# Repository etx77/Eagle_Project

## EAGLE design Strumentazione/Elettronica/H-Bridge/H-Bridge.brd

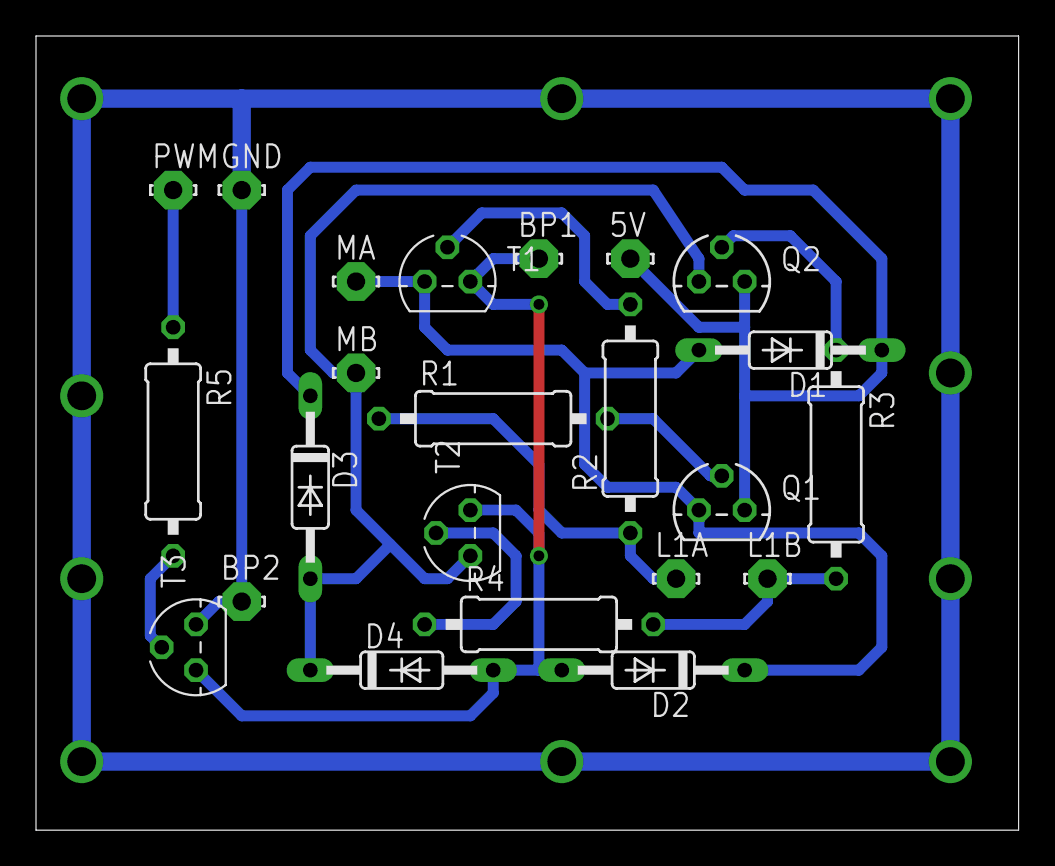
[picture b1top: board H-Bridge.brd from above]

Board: 2 copper layers, 54.6 x 44.1 mm, 23 parts (0 on the bottom side), 13 nets.

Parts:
5V: LSP10
BP1, BP2: LSP10
D1, D2, D3, D4: 1N4148DO35-10; DO35-10
GND: LSP10
L1A, L1B: LSP10
MA: LSP10
MB: LSP10
PWM: LSP10
Q1, Q2: BC557; TO92
R1, R2, R3, R4: 10k; 0309/12
R5: 1k2; 0309/12
T1, T2, T3: BC547; TO92

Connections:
unnamed: L1A.MP, R1.1, R2.1
unnamed: Q1.2, R1.2
unnamed: R2.2, T1.2
unnamed: D1.A, D2.C, MA.MP, Q1.3, T1.3
unnamed: D3.A, D4.C, MB.MP, Q2.3, T2.3
unnamed: Q2.2, R3.1
unnamed: R4.1, T2.2
unnamed: L1B.MP, R3.2, R4.2
unnamed: BP1.MP, D2.A, D4.A, T1.1, T2.1, T3.3
unnamed: 5V.MP, D1.C, D3.C, Q1.1, Q2.1
unnamed: R5.2, T3.2
unnamed: PWM.MP, R5.1
unnamed: BP2.MP, GND.MP, T3.1

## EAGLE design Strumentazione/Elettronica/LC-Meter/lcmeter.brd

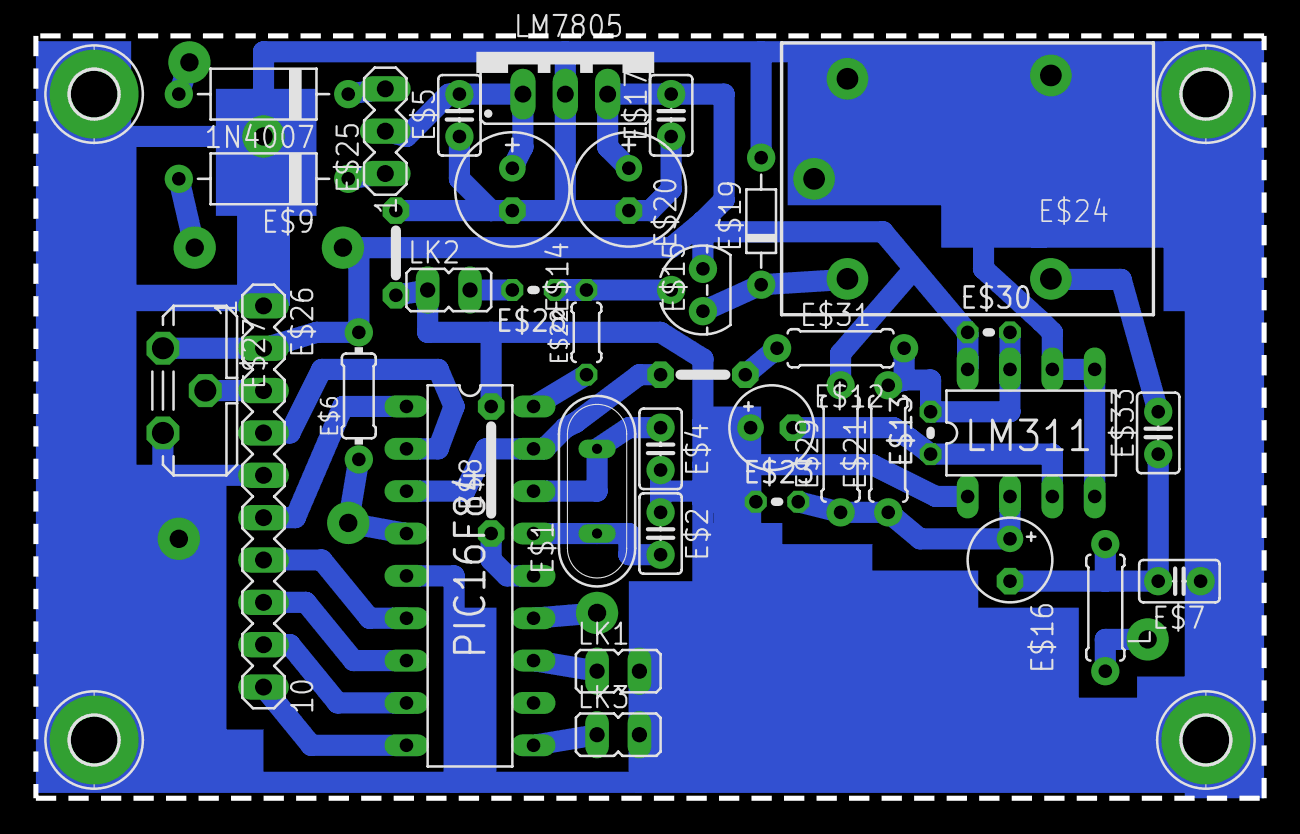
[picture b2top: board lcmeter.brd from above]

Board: 2 copper layers, 73.7 x 45.7 mm, 42 parts (0 on the bottom side), 29 nets.

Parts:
1N4007: 1N4007; D-10
E$1: 4MHz; QS
E$2, E$4: 33pF; C2.5-2
E$3: Vcc; 05
E$5, E$17: 0.1; C2.5-2
E$6: 6.8K; 0204/7
E$7, E$33: 1nF; C2.5-2
E$8: 07
E$9: 1N4007; D-10
E$12, E$16: 10uF; E2,5-5
E$13: 47K; 0204V
E$14, E$15: 22uF; E2,5-7
E$19: 1N914; D-7.5
E$20: PNP; TO92
E$21, E$29: 100K; 0207/7
E$22: 6.8K; 0204/5
E$23: 100K; 0204V
E$24: Rele; ZN5
E$25: MA03-1
E$26: MA10-1
E$27: 10K; ST10
E$28: 6.8K; 0204V
E$30: 1K; 0204V
E$31: 6.8K; 0207/7
E$32: 05
E$34, E$35, E$36, E$37: 2,8-PAD
L: 82uH; 0207/7
LK1, LK2, LK3: JP1
LM311: LM311; DIL8
LM7805: LM7805; 78XXS
PIC16F84: PIC16F84; DIL18

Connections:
GND: E$2.1, E$3.1, E$3.2, E$4.2, E$5.1, E$8.2, E$14.-, E$15.-, E$17.1, E$19.A, E$23.1, E$24.11, E$26.1, E$26.5, LK1.2, LK2.1, LK3.2, LM311.1, LM7805.GND, PIC16F84.5
S$2: E$1.1, E$2.2, PIC16F84.15
S$3: E$9.C, E$25.1
S$4: E$1.2, E$4.1, PIC16F84.16
S$5: E$30.1, LM311.8
S$6: 1N4007.C, E$25.3
S$7: E$26.6, PIC16F84.1
S$8: E$26.3, E$27.S
S$9: E$5.2, E$14.+, E$25.2, LM7805.IN
S$10: E$26.4, PIC16F84.2
S$11: E$13.1, LM311.3
S$13: LK3.1, PIC16F84.10
S$14: E$28.2, LK2.2
S$15: E$20.2, E$28.1
S$17: E$19.C, E$20.1
S$19: E$6.1, PIC16F84.4
S$22: E$30.2, LM311.7
S$23: E$21.1, E$23.2
S$24: E$21.2, E$31.2
S$27: E$32.1, PIC16F84.3, PIC16F84.17
S$28: E$31.1, E$32.2
S$29: E$16.-, E$33.1, L.1
S$30: E$26.10, PIC16F84.9
S$32: E$26.8, PIC16F84.7
S$33: E$26.7, PIC16F84.6
S$34: LK1.1, PIC16F84.12
S$36: LM311.5, LM311.6
S$37: E$8.1, PIC16F84.14
VCC: E$9.A, E$15.+, E$17.2, E$20.3, E$26.2, E$27.A, L.2, LM7805.OUT, PIC16F84.13

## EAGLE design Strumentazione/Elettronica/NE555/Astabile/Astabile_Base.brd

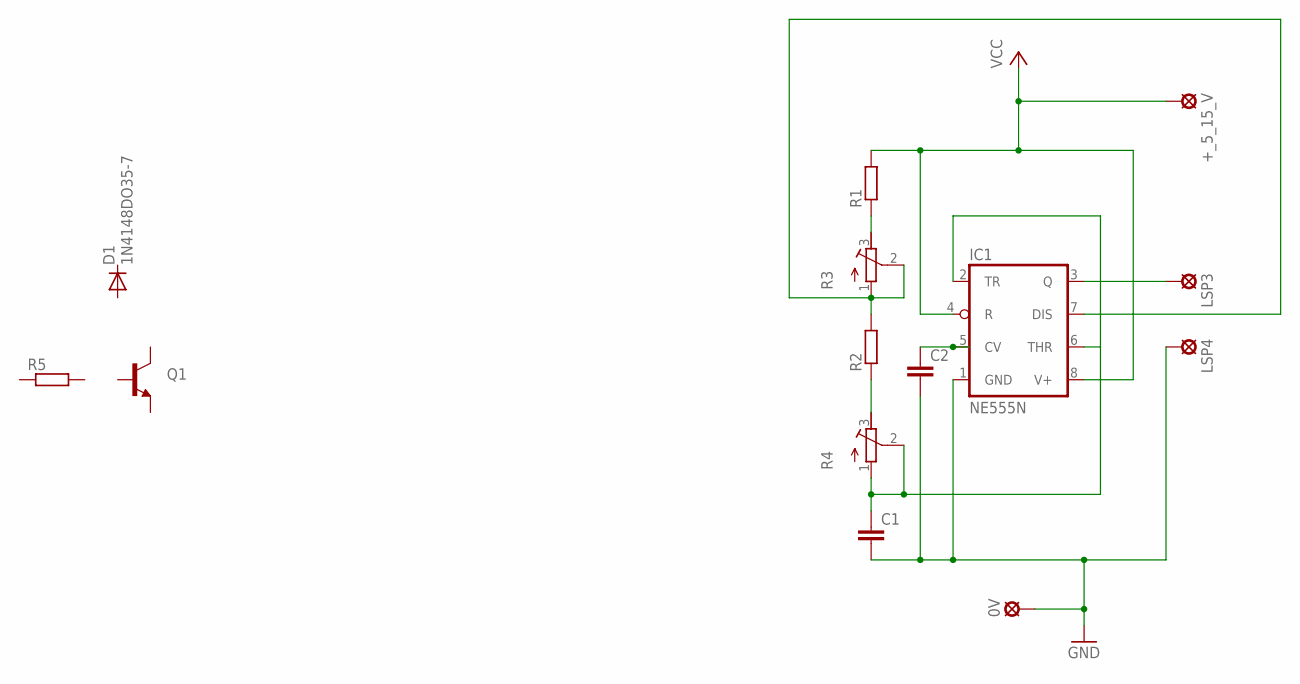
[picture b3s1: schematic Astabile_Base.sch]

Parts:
0V: LSP10
+_5_15_V: LSP10
C1, C2: C-EU050-024X044; C050-024X044
D1: 1N4148DO35-7; DO35-7
IC1: NE555N; DIL08
LSP3, LSP4: LSP10
Q1: TRANSISTOR_NPNBC547; TO-92-AMMO
R1, R2: R-EU_0204/7; 0204/7
R3, R4: R-TRIMM3339P; RTRIM3339P
R5: R-EU_0207/2V; 0207/2V

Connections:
GND: 0V.MP, C1.2, C2.2, IC1.1 (GND), LSP4.MP
unnamed: IC1.3 (Q), LSP3.MP
unnamed: R1.1, R3.3 (E)
unnamed: IC1.7 (DIS), R2.2, R3.1 (A), R3.2 (S)
unnamed: R2.1, R4.3 (E)
unnamed: C1.1, IC1.2 (TR), IC1.6 (THR), R4.1 (A), R4.2 (S)
unnamed: C2.1, IC1.5 (CV)
VCC: +_5_15_V.MP, IC1.4 (R), IC1.8 (V+), R1.2

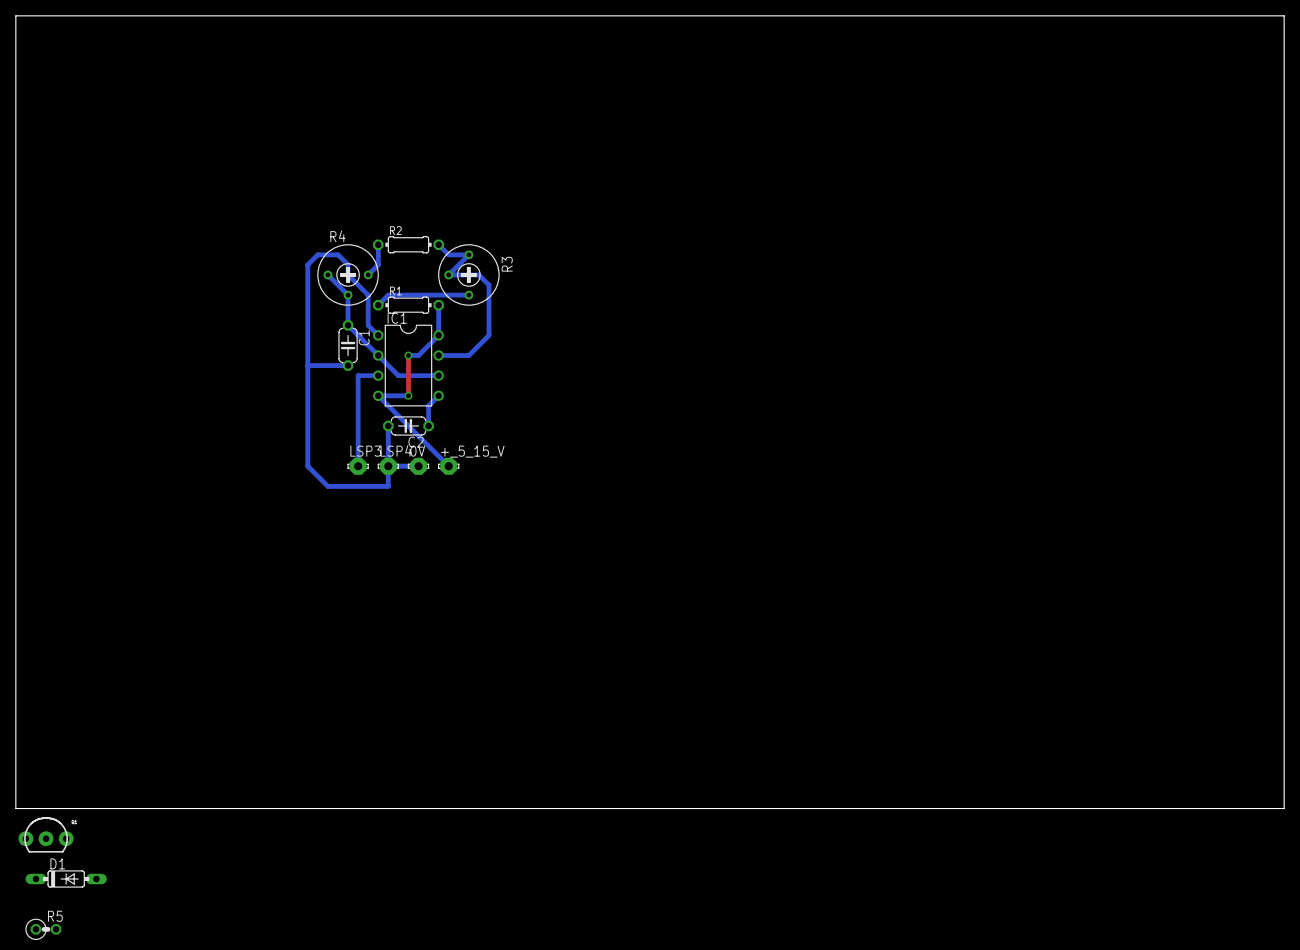
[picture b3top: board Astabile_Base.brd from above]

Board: 2 copper layers, 160.0 x 100.0 mm, 14 parts (0 on the bottom side), 8 nets.

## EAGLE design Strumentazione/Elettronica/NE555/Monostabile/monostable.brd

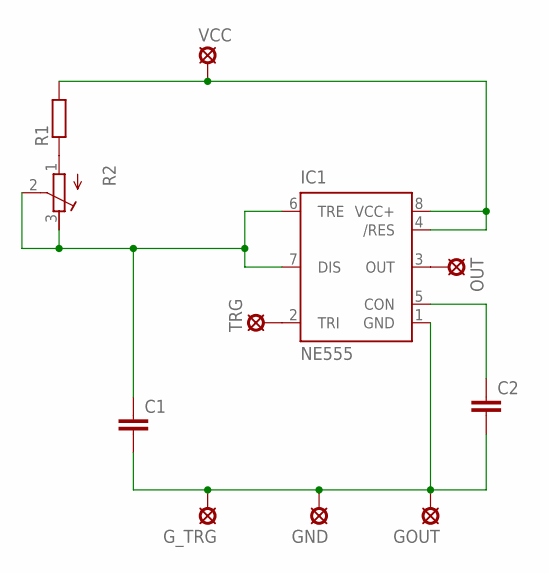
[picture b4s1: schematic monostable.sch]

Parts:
C1, C2: C-EU050-024X044; C050-024X044
GND: LSP10
GOUT: LSP10
G_TRG: LSP10
IC1: NE555; DIL-08
OUT: LSP10
R1: R-EU_0207/10; 0207/10
R2: R-TRIMM3339P; RTRIM3339P
TRG: LSP10
VCC: LSP10

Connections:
unnamed: C1.2, C2.2, GND.MP, GOUT.MP, G_TRG.MP, IC1.1 (GND)
unnamed: C1.1, IC1.6 (TRE), IC1.7 (DIS), R2.2 (S), R2.3 (E)
unnamed: C2.1, IC1.5 (CON)
unnamed: IC1.4 (/RES), IC1.8 (VCC+), R1.2, VCC.MP
unnamed: IC1.2 (TRI), TRG.MP
unnamed: IC1.3 (OUT), OUT.MP
unnamed: R1.1, R2.1 (A)

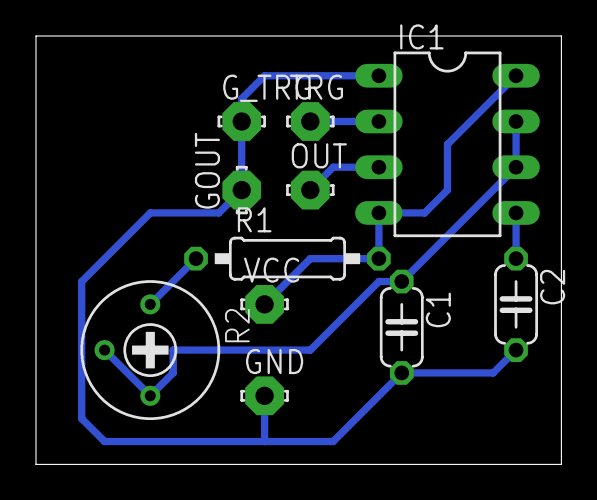
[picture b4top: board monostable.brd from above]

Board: 2 copper layers, 29.2 x 23.8 mm, 11 parts (0 on the bottom side), 7 nets.

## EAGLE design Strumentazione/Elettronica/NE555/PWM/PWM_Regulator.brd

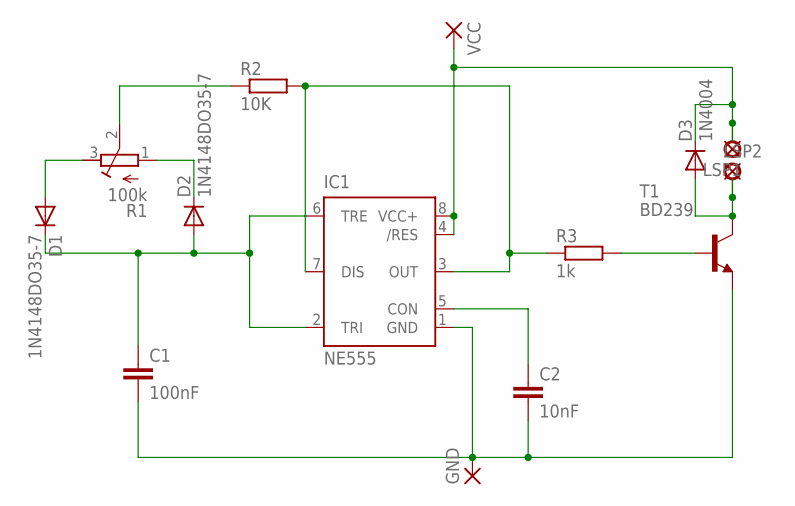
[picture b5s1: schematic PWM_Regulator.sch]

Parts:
C1: 100nF; C050-024X044
C2: 10nF; C050-024X044
D1, D2: 1N4148DO35-7; DO35-7
D3: 1N4004; DO41-10
GND: 2,54/0,8
IC1: NE555; DIL-08
LSP1, LSP2: LSP10
R1: 100k; RTRIM3339P
R2: 10K; 0204/7
R3: 1k; 0207/10
T1: BD239; TO220
VCC: 2,54/0,8

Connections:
unnamed: D1.A, R1.3 (E)
unnamed: D2.C, R1.1 (A)
unnamed: C1.1, D1.C, D2.A, IC1.2 (TRI), IC1.6 (TRE)
unnamed: R3.2, T1.1 (B)
unnamed: C2.1, IC1.5 (CON)
unnamed: D3.C, IC1.4 (/RES), IC1.8 (VCC+), LSP1.MP, VCC.1
unnamed: IC1.3 (OUT), IC1.7 (DIS), R2.2, R3.1
unnamed: R1.2 (S), R2.1
unnamed: C1.2, C2.2, GND.1, IC1.1 (GND), T1.3 (E)
unnamed: D3.A, LSP2.MP, T1.2 (C)

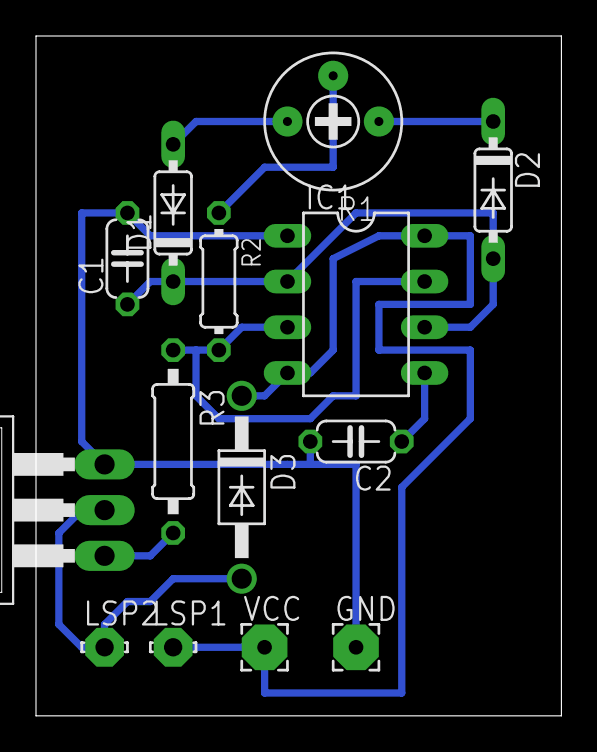
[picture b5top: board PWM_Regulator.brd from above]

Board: 2 copper layers, 29.2 x 37.8 mm, 14 parts (0 on the bottom side), 10 nets.

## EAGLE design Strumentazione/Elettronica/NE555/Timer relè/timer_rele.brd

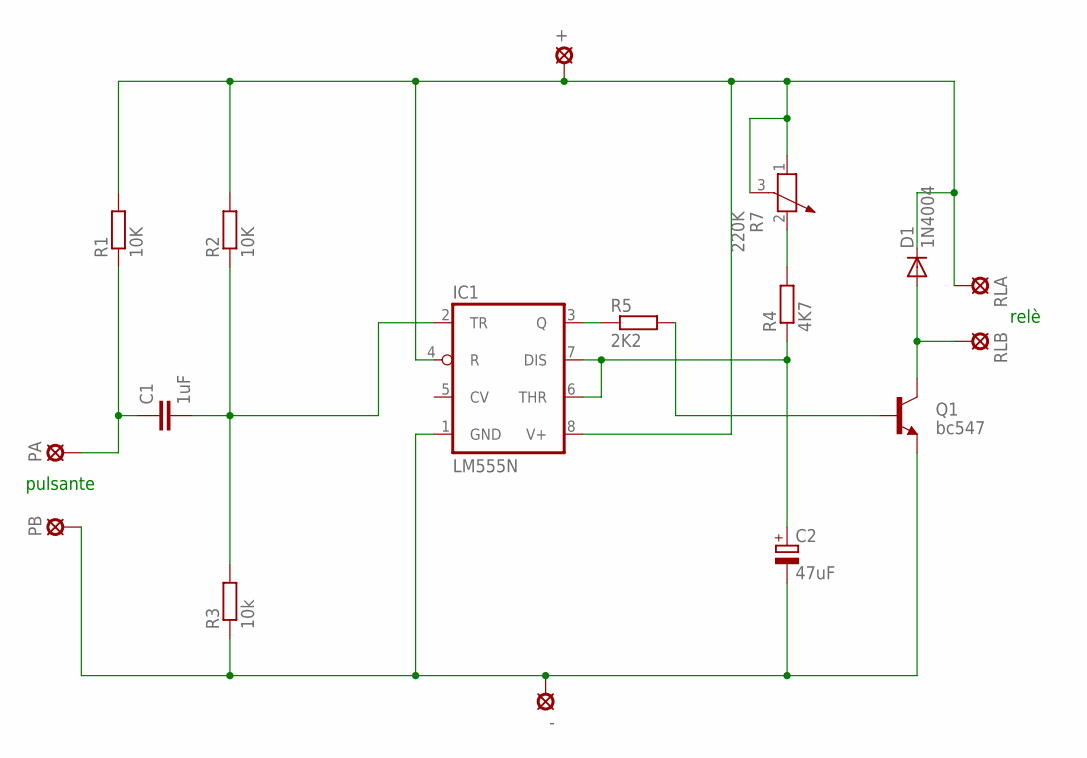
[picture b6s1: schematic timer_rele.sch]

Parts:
+: LSP10
-: LSP10
C1: 1uF; C050-030X075
C2: 47uF; E2-5
D1: 1N4004; DO41-10
IC1: LM555N; DIL08
PA: LSP10
PB: LSP10
Q1: bc547; TO-92-AMMO
R1, R2: 10K; 0207/10
R3: 10k; 0207/10
R4: 4K7; 0207/10
R5: 2K2; 0207/10
R7: 220K; PT-10
RLA: LSP10
RLB: LSP10

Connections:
unnamed: +.MP, D1.C, IC1.4 (R), IC1.8 (V+), R1.2, R2.2, R7.1, R7.3, RLA.MP
unnamed: D1.A, Q1.1 (C), RLB.MP
unnamed: -.MP, C2.-, IC1.1 (GND), PB.MP, Q1.3 (E), R3.1
unnamed: C1.1, PA.MP, R1.1
unnamed: C1.2, IC1.2 (TR), R2.1, R3.2
unnamed: IC1.3 (Q), R5.1
unnamed: Q1.2 (B), R5.2
unnamed: R4.2, R7.2
unnamed: C2.+, IC1.6 (THR), IC1.7 (DIS), R4.1

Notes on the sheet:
pulsante
relè

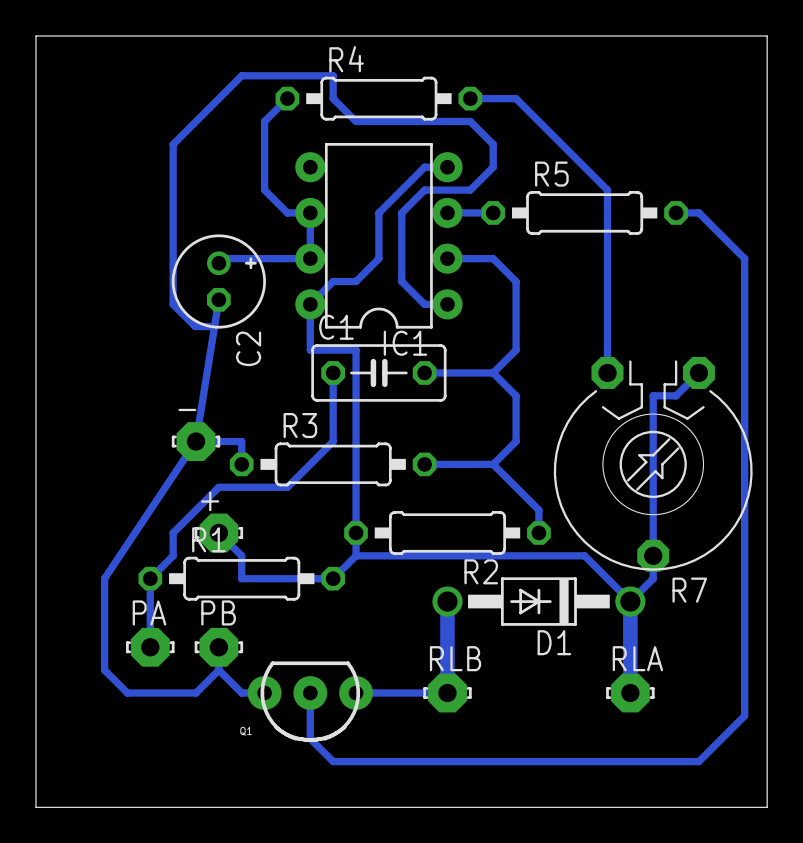
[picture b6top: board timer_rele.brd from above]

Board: 2 copper layers, 40.6 x 42.9 mm, 17 parts (0 on the bottom side), 9 nets.

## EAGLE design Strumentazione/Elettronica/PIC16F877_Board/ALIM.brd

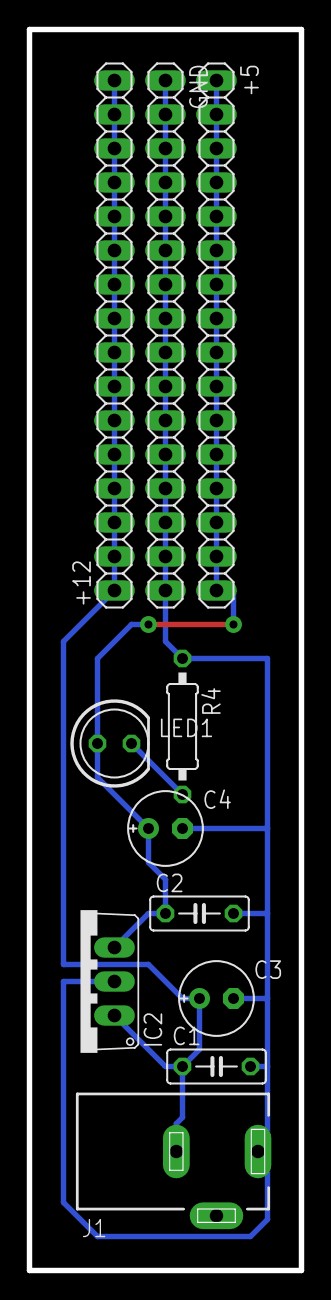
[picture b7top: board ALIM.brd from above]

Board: 2 copper layers, 20.3 x 92.7 mm, 11 parts (0 on the bottom side), 4 nets.

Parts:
+5, +12: 1X16
C1, C2: C050-025X075
C3, C4: E2,5-6E
GND: 1X16
IC2: 7805TV; TO220V
J1: DCJ0303
LED1: RED; LED5MM
R4: 220; 0207/10

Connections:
unnamed: LED1.K, R4.2
unnamed: C1.2, C2.2, C3.-, C4.-, GND.1, GND.2, GND.3, GND.4, GND.5, GND.6, GND.7, GND.8, GND.9, GND.10, GND.11, GND.12, GND.13, GND.14, GND.15, GND.16, IC2.2, J1.1, R4.1
unnamed: +12.1, +12.2, +12.3, +12.4, +12.5, +12.6, +12.7, +12.8, +12.9, +12.10, +12.11, +12.12, +12.13, +12.14, +12.15, +12.16, C1.1, C3.+, IC2.1, J1.3
unnamed: +5.1, +5.2, +5.3, +5.4, +5.5, +5.6, +5.7, +5.8, +5.9, +5.10, +5.11, +5.12, +5.13, +5.14, +5.15, +5.16, C2.1, C4.+, IC2.3, LED1.A

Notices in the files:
parts and their libraries:
SparkFun-DiscreteSemi: Licensing: Creative Commons ShareAlike 4.0 International - https://creativecommons.org/licenses/by-sa/4.0
